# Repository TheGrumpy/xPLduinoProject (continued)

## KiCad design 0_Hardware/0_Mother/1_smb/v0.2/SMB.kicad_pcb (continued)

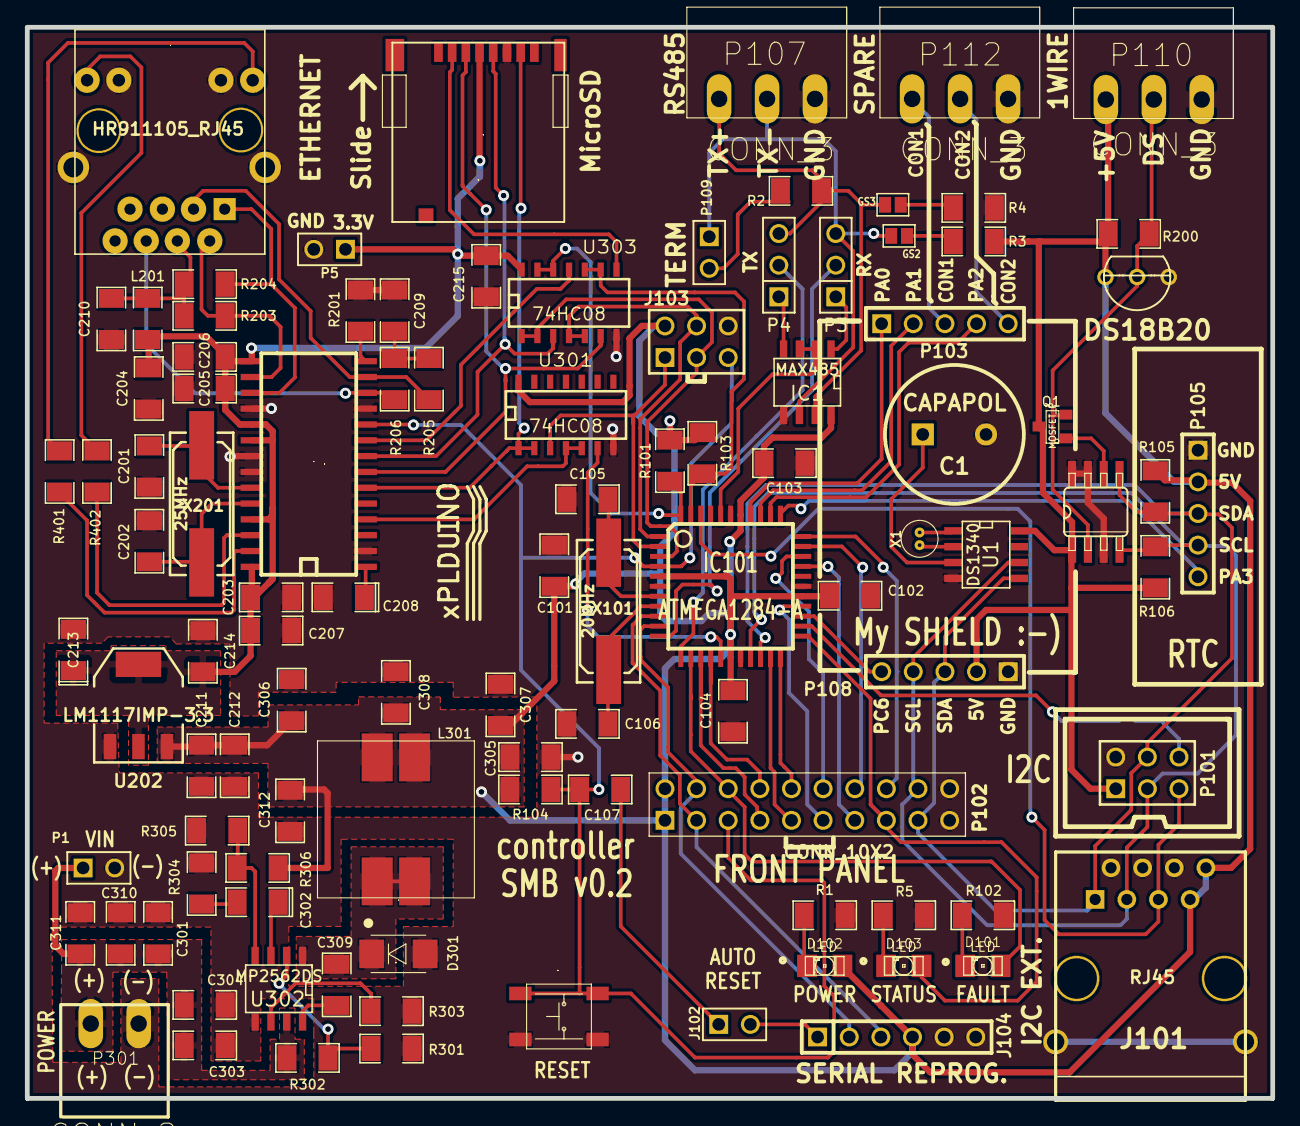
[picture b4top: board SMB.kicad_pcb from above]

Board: 2 copper layers, 100.0 x 86.0 mm, 105 parts (0 on the bottom side), 85 nets.

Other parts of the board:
logo_xplduino: VAL**; logo_xplduino

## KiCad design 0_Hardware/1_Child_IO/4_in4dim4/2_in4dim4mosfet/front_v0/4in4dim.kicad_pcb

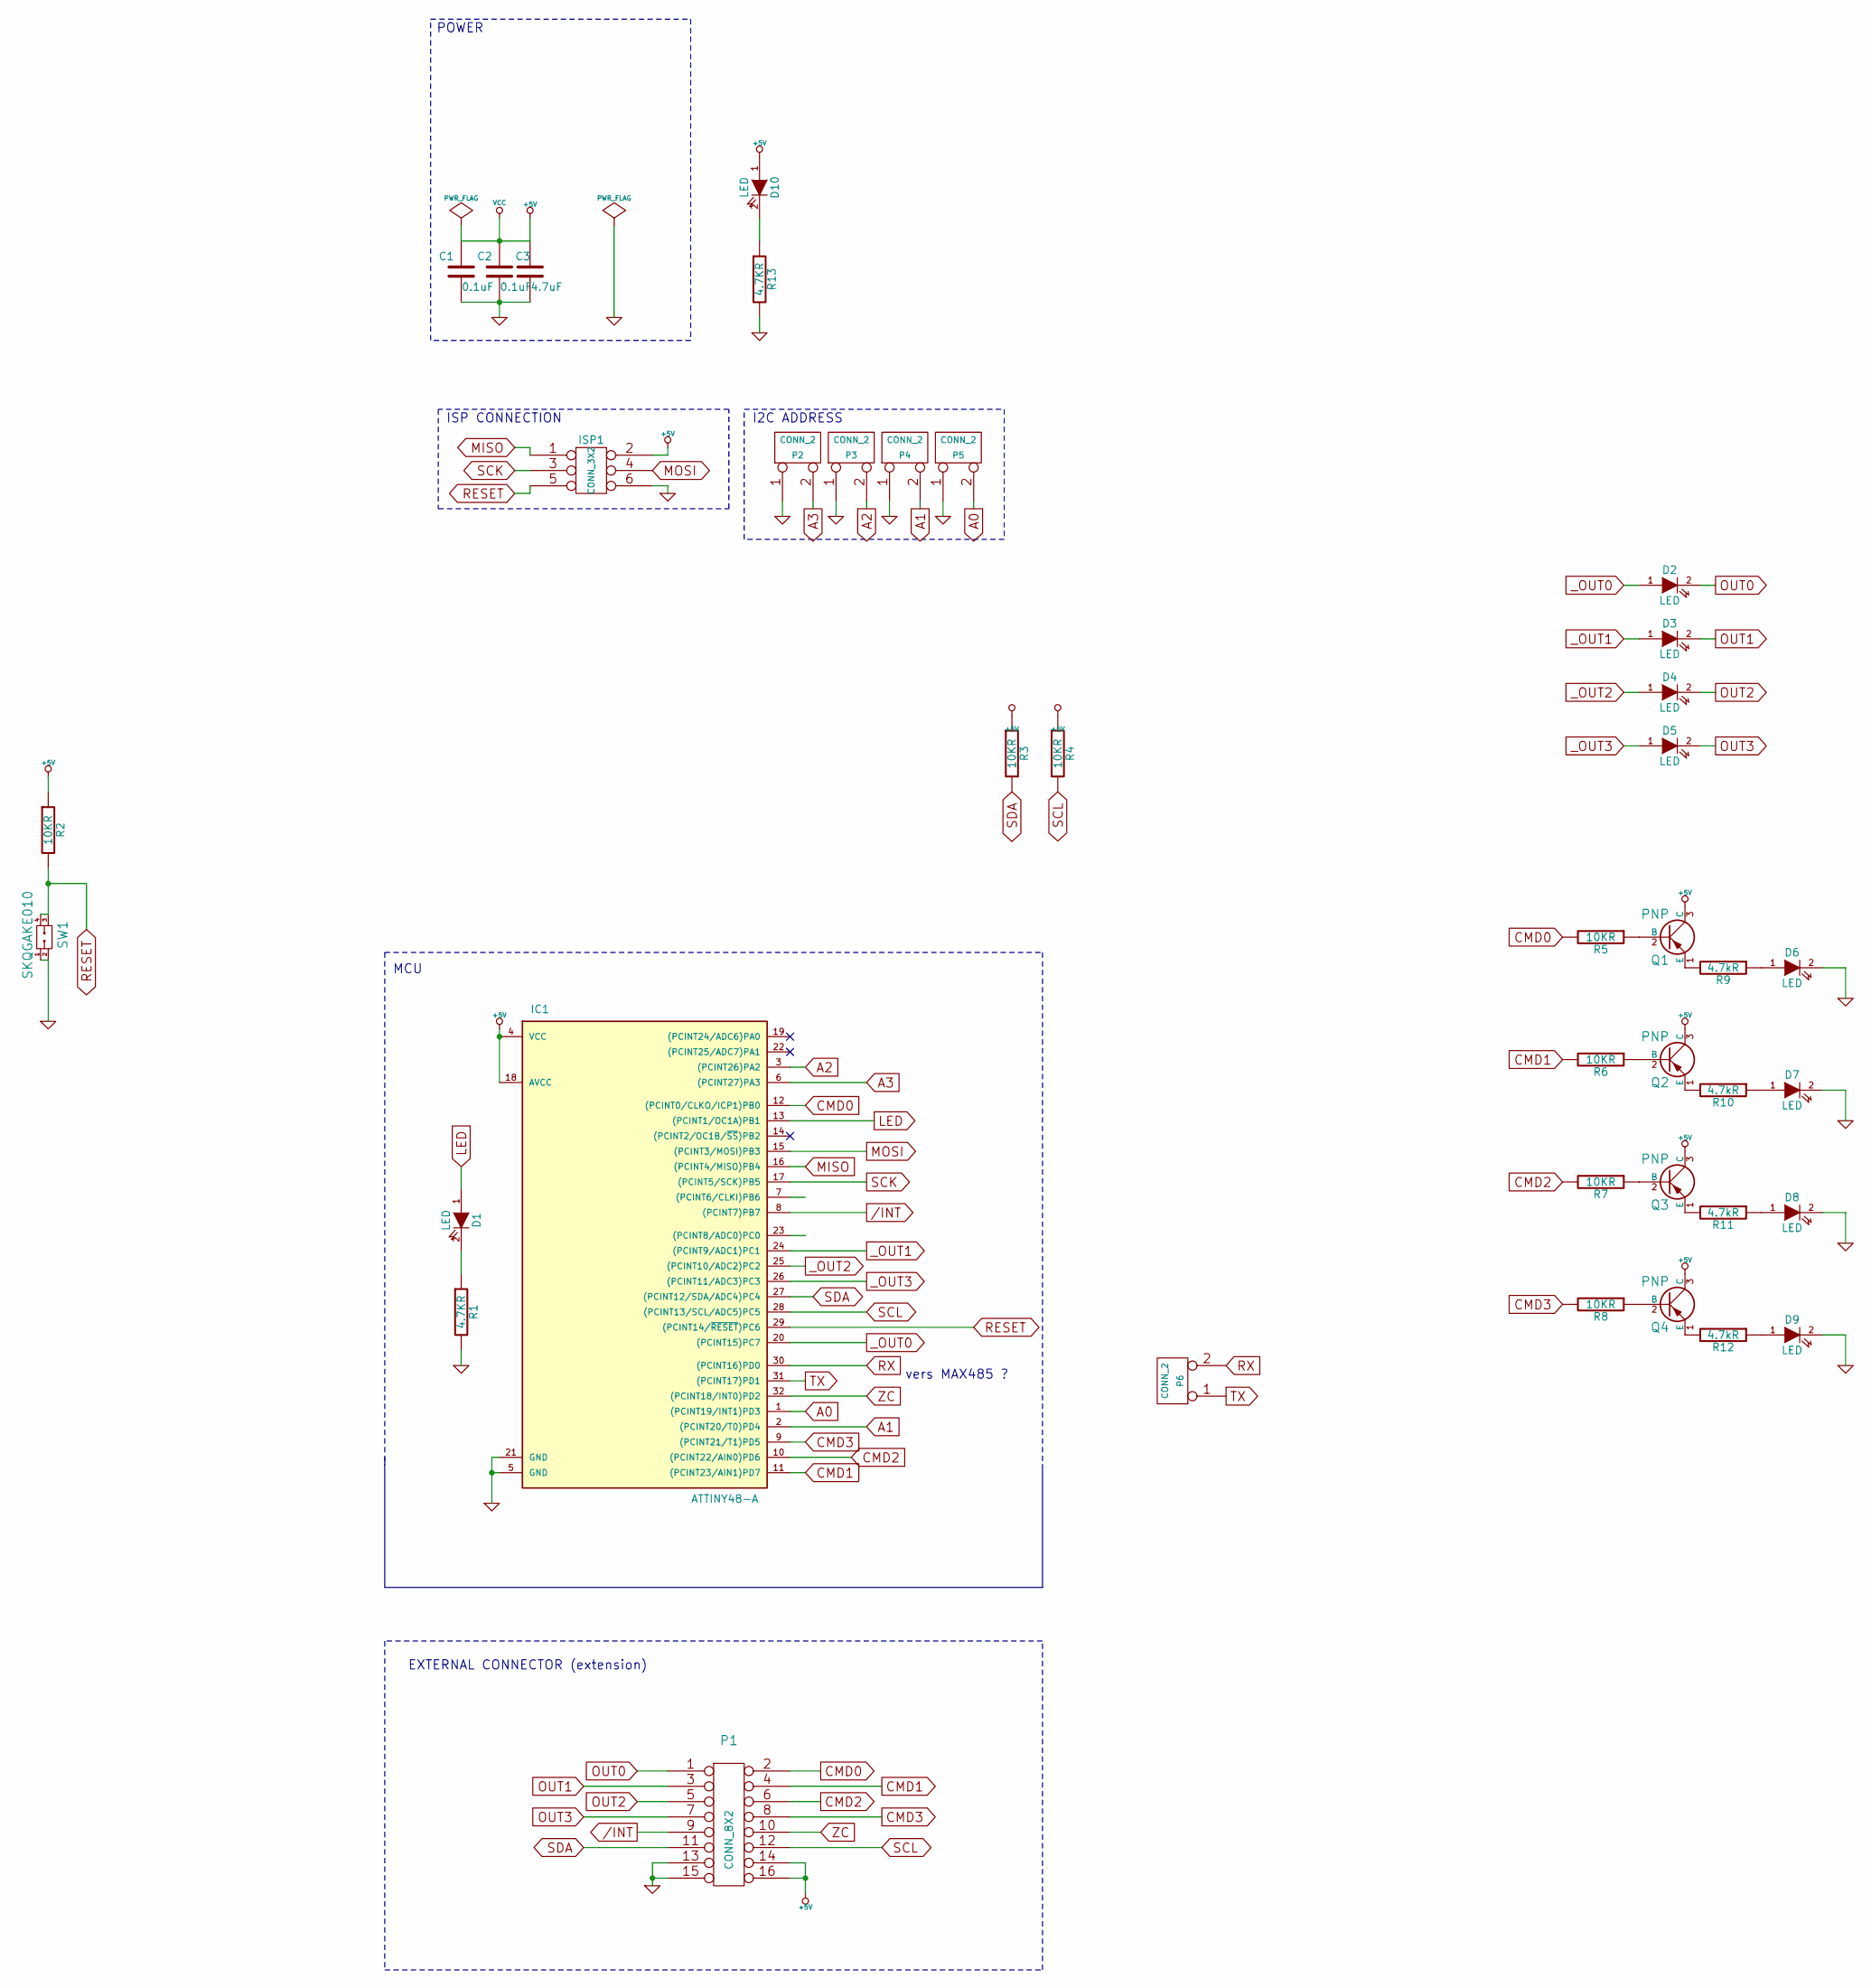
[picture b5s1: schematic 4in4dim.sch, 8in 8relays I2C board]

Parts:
C1, C2: 0.1uF
C3: 4.7uF
D1, D2, D3, D4, D5, D6, D7, D8, D9, D10: LED
IC1: ATTINY48-A; TQFP32
ISP1: CONN_3X2
P1: CONN_8X2
P2, P3, P4, P5, P6: CONN_2
Q1, Q2, Q3, Q4: PNP
R1, R13: 4.7KR
R2, R3, R4, R5, R6, R7, R8: 10KR
R9, R10, R11, R12: 4.7kR
SW1: SKQGAKE010

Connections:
+5V: C1.1, C2.1, C3.1, D10.1 (A), IC1.4 (VCC), IC1.18 (AVCC), ISP1.2, P1.14, P1.16, Q1.3 (C), Q2.3 (C), Q3.3 (C), Q4.3 (C), R2.1, R3.1, R4.1
/INT: IC1.8 ((PCINT7)PB7), P1.9
A0: IC1.1 ((PCINT19/INT1)PD3), P5.2 (PM)
A1: IC1.2 ((PCINT20/T0)PD4), P4.2 (PM)
A2: IC1.3 ((PCINT26)PA2), P3.2 (PM)
A3: IC1.6 ((PCINT27)PA3), P2.2 (PM)
CMD0: IC1.12 ((PCINT0/CLKO/ICP1)PB0), P1.2, R5.2
CMD1: IC1.11 ((PCINT23/AIN1)PD7), P1.4, R6.2
CMD2: IC1.10 ((PCINT22/AIN0)PD6), P1.6, R7.2
CMD3: IC1.9 ((PCINT21/T1)PD5), P1.8, R8.2
GND: C1.2, C2.2, C3.2, D6.2 (K), D7.2 (K), D8.2 (K), D9.2 (K), IC1.5 (GND), IC1.21 (GND), ISP1.6, P1.13, P1.15, P2.1, P3.1, P4.1, P5.1, R1.2, R13.2, SW1.1, SW1.2
LED: D1.1 (A), IC1.13 ((PCINT1/OC1A)PB1)
MISO: IC1.16 ((PCINT4/MISO)PB4), ISP1.1
MOSI: IC1.15 ((PCINT3/MOSI)PB3), ISP1.4
unnamed: D10.2 (K), R13.1
unnamed: D9.1 (A), R12.1
unnamed: D1.2 (K), R1.1
unnamed: D7.1 (A), R10.1
unnamed: Q2.1 (E), R10.2
unnamed: Q2.2 (B), R6.1
unnamed: Q3.1 (E), R11.2
unnamed: D6.1 (A), R9.1
unnamed: Q1.1 (E), R9.2
unnamed: Q4.1 (E), R12.2
unnamed: Q4.2 (B), R8.1
unnamed: D8.1 (A), R11.1
unnamed: Q3.2 (B), R7.1
unnamed: Q1.2 (B), R5.1
OUT0: D2.2 (K), P1.1
OUT1: D3.2 (K), P1.3
OUT2: D4.2 (K), P1.5
OUT3: D5.2 (K), P1.7
RESET: IC1.29 ((PCINT14/~RESET~)PC6), ISP1.5, R2.2, SW1.3, SW1.4
RX: IC1.30 ((PCINT16)PD0), P6.2 (PM)
SCK: IC1.17 ((PCINT5/SCK)PB5), ISP1.3
SCL: IC1.28 ((PCINT13/SCL/ADC5)PC5), P1.12, R4.2
SDA: IC1.27 ((PCINT12/SDA/ADC4)PC4), P1.11, R3.2
TX: IC1.31 ((PCINT17)PD1), P6.1
ZC: IC1.32 ((PCINT18/INT0)PD2), P1.10
_OUT0: D2.1 (A), IC1.20 ((PCINT15)PC7)
_OUT1: D3.1 (A), IC1.24 ((PCINT9/ADC1)PC1)
_OUT2: D4.1 (A), IC1.25 ((PCINT10/ADC2)PC2)
_OUT3: D5.1 (A), IC1.26 ((PCINT11/ADC3)PC3)

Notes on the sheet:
ISP CONNECTION
I2C ADDRESS
POWER
MCU
EXTERNAL CONNECTOR (extension)
vers MAX485 ?

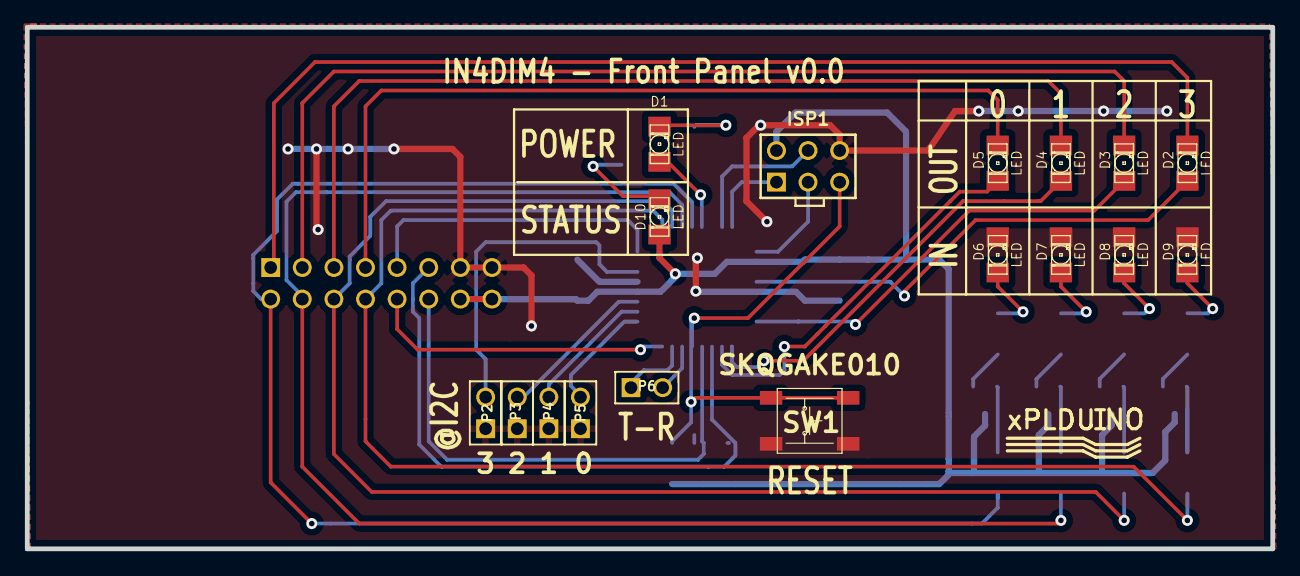
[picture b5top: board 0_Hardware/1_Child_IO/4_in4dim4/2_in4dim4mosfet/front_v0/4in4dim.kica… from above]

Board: 2 copper layers, 100.1 x 41.9 mm, 40 parts (0 on the bottom side), 43 nets.

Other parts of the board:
logo_xplduino: VAL**; logo_xplduino

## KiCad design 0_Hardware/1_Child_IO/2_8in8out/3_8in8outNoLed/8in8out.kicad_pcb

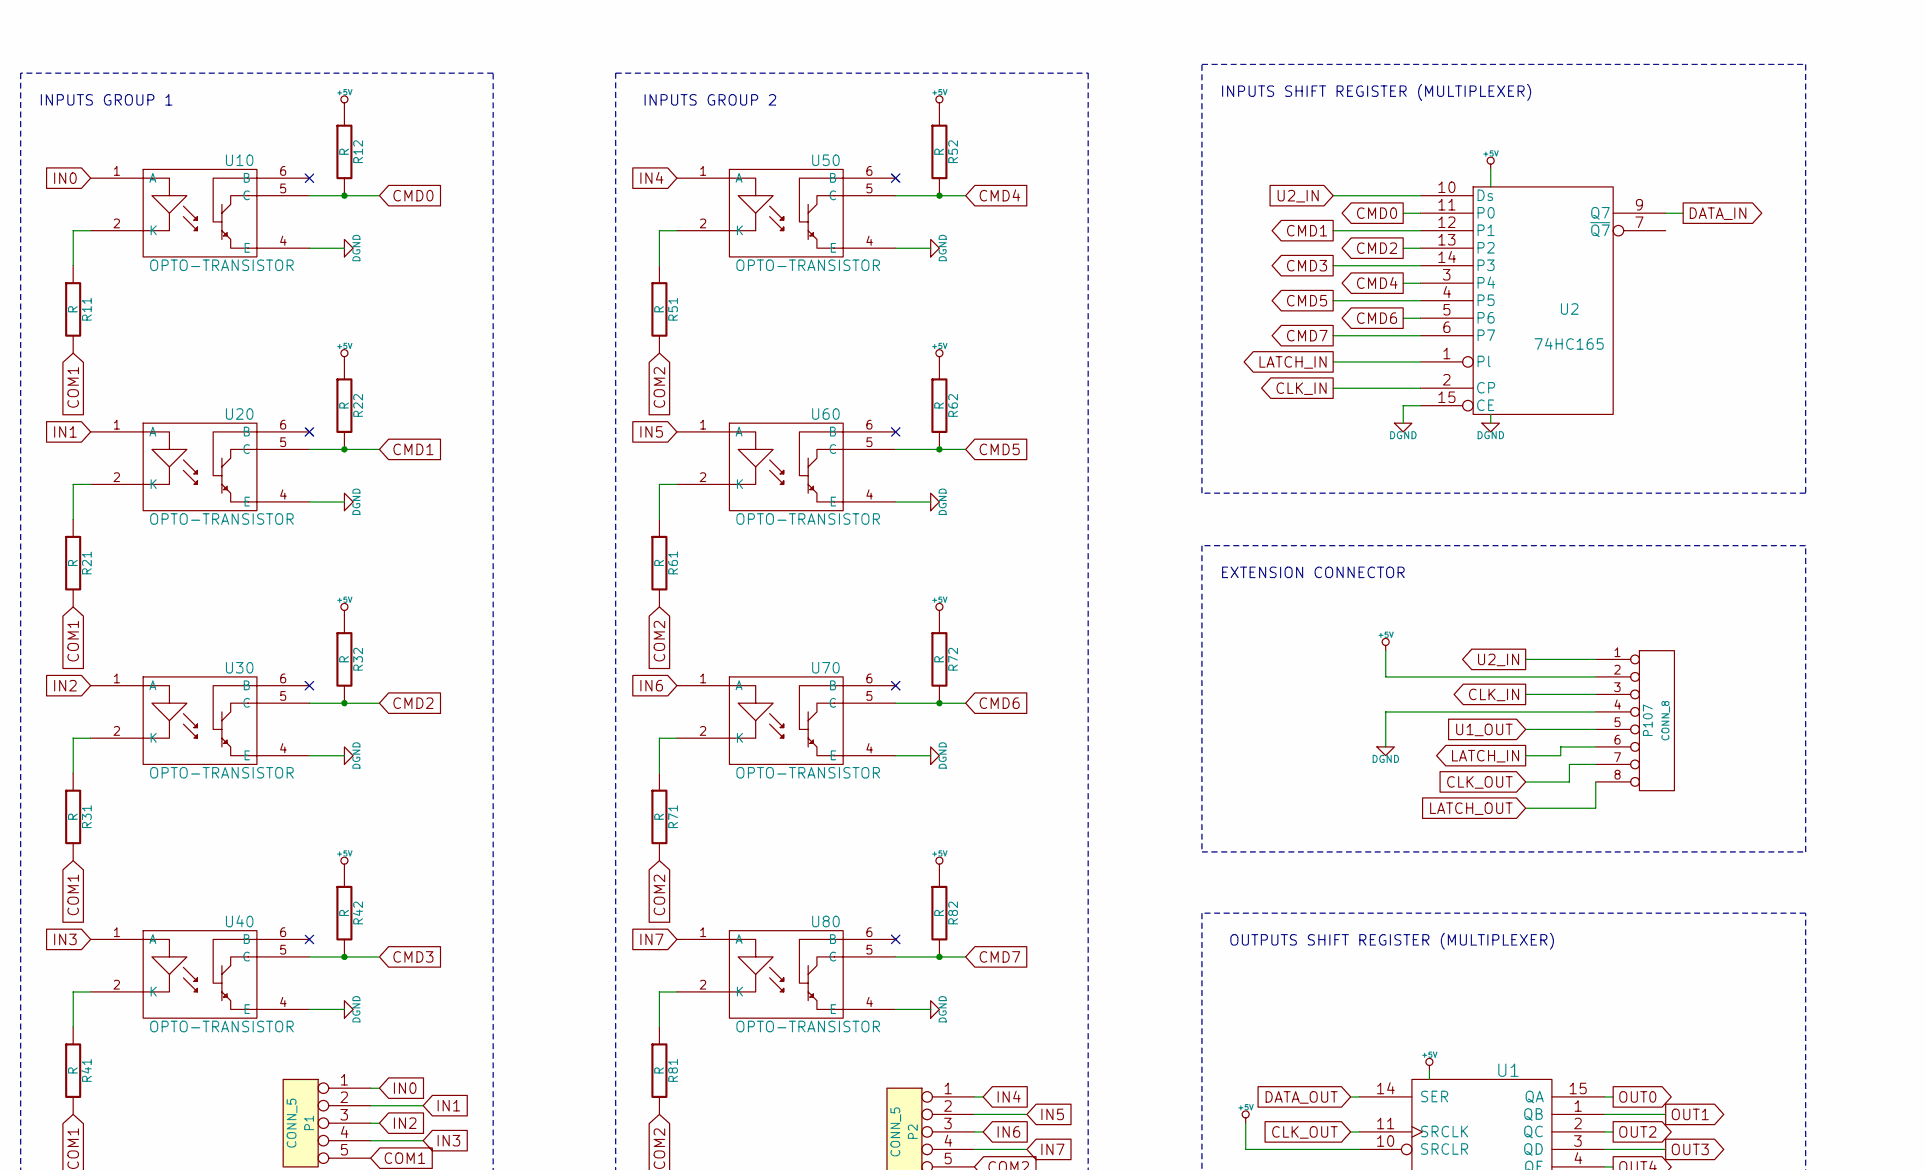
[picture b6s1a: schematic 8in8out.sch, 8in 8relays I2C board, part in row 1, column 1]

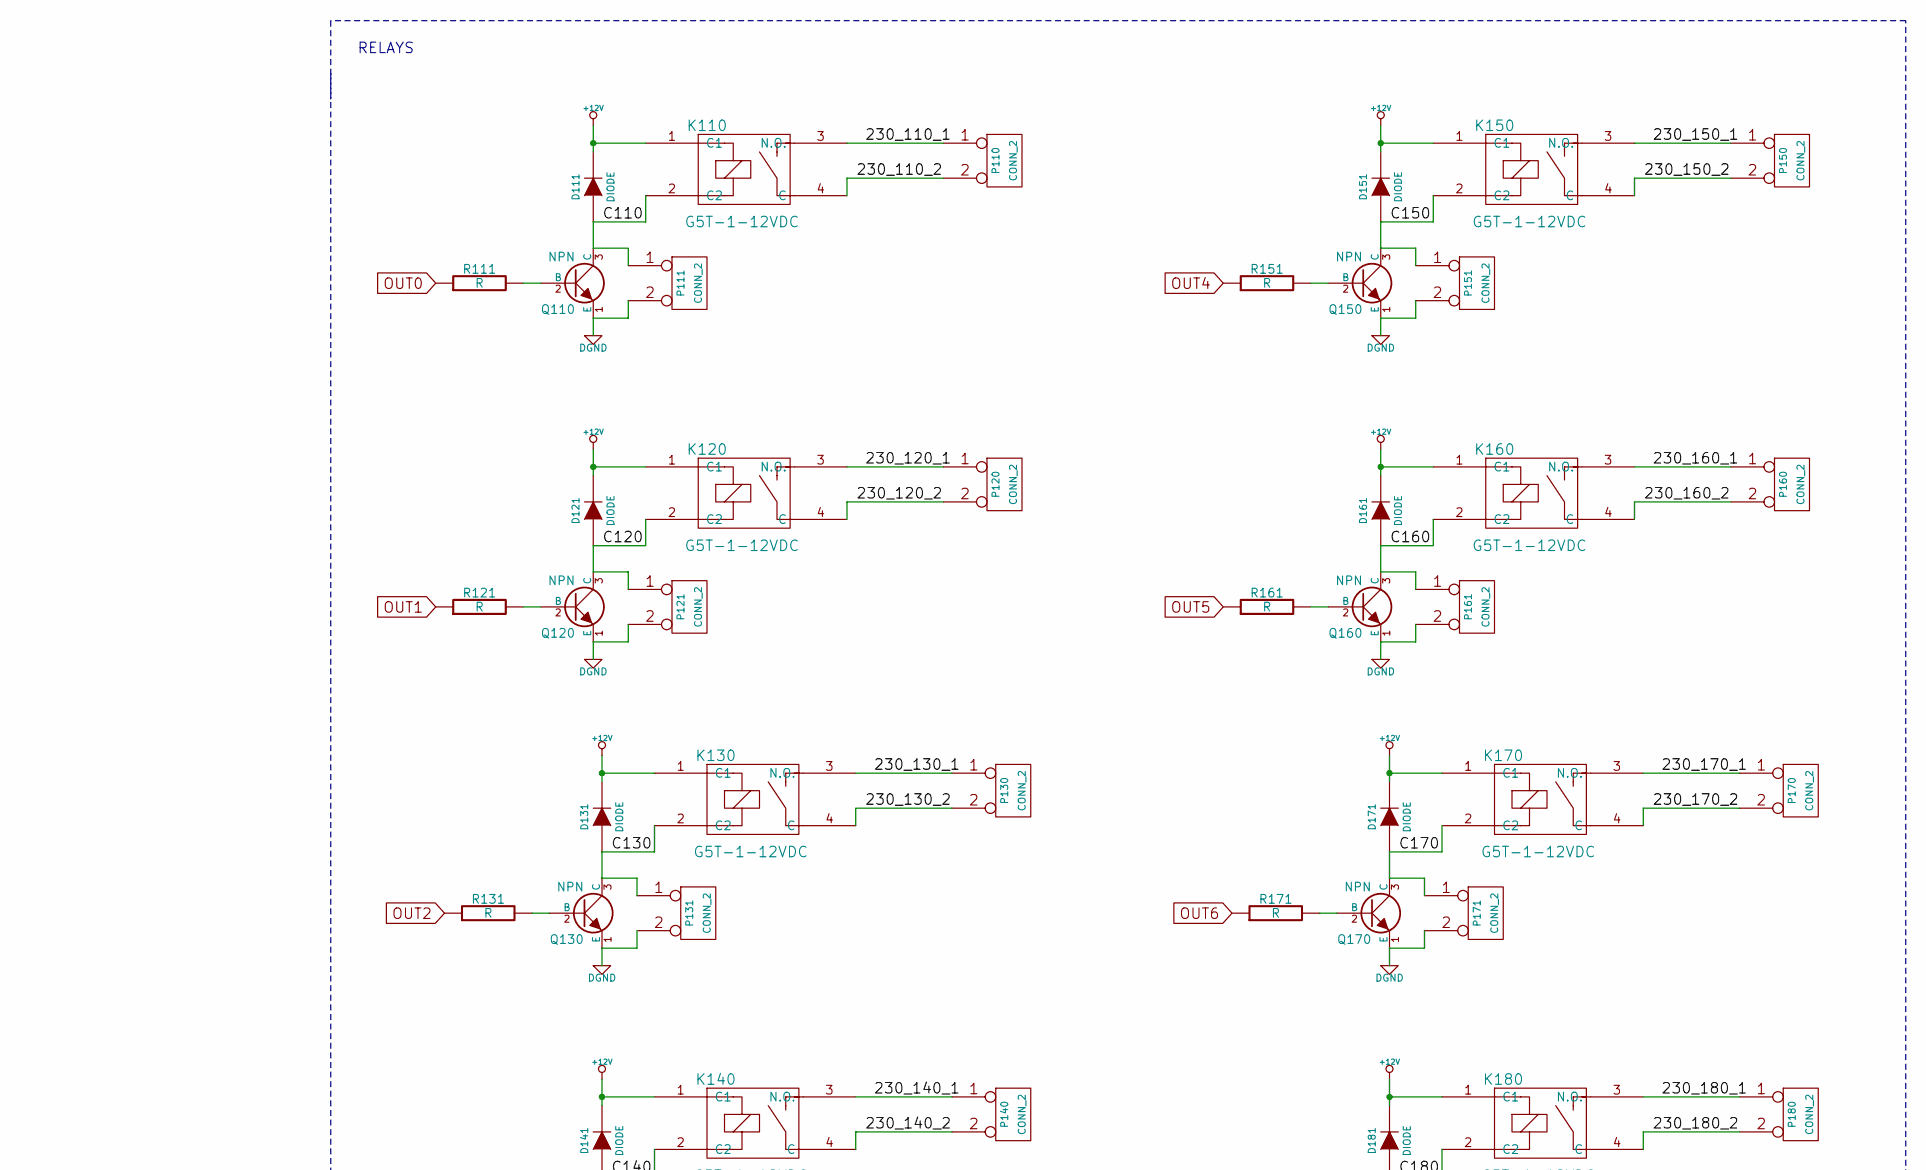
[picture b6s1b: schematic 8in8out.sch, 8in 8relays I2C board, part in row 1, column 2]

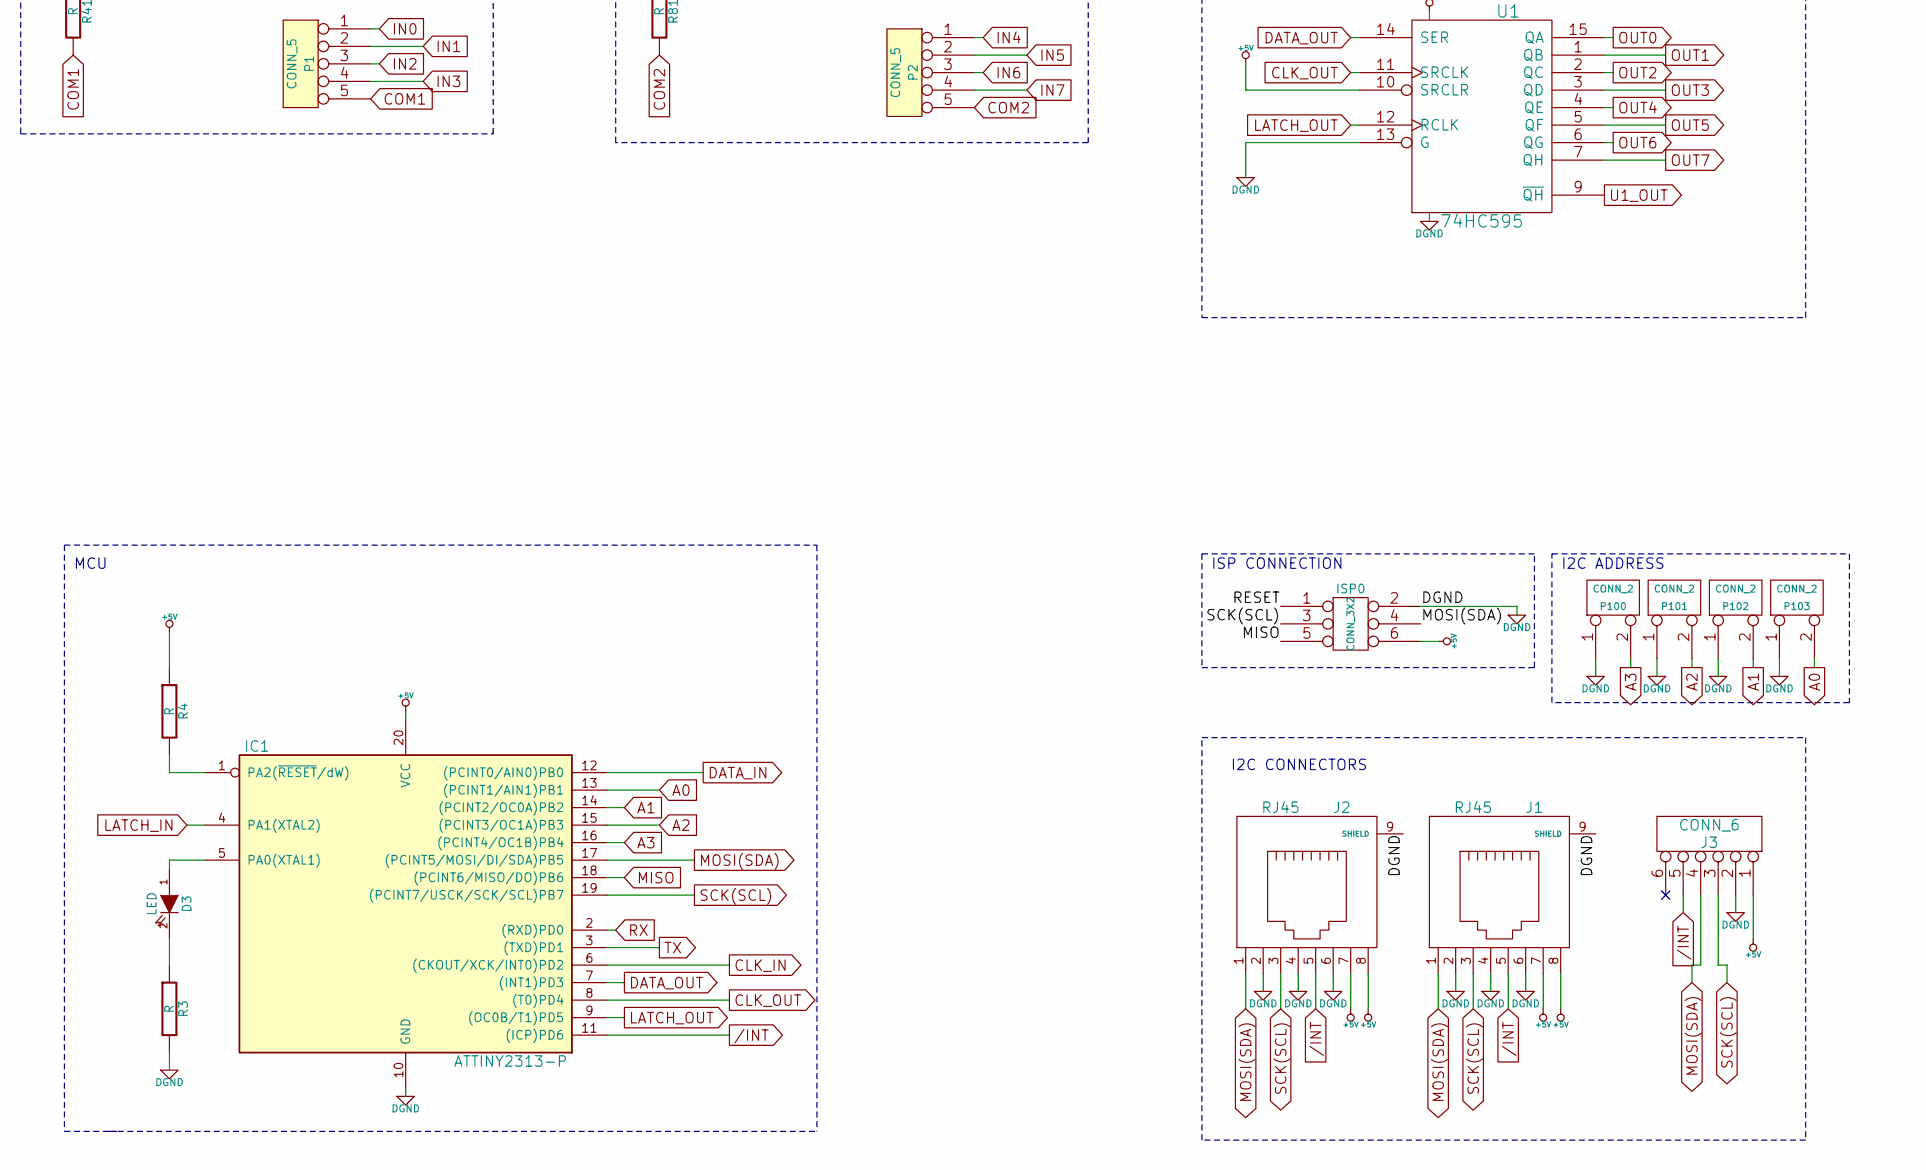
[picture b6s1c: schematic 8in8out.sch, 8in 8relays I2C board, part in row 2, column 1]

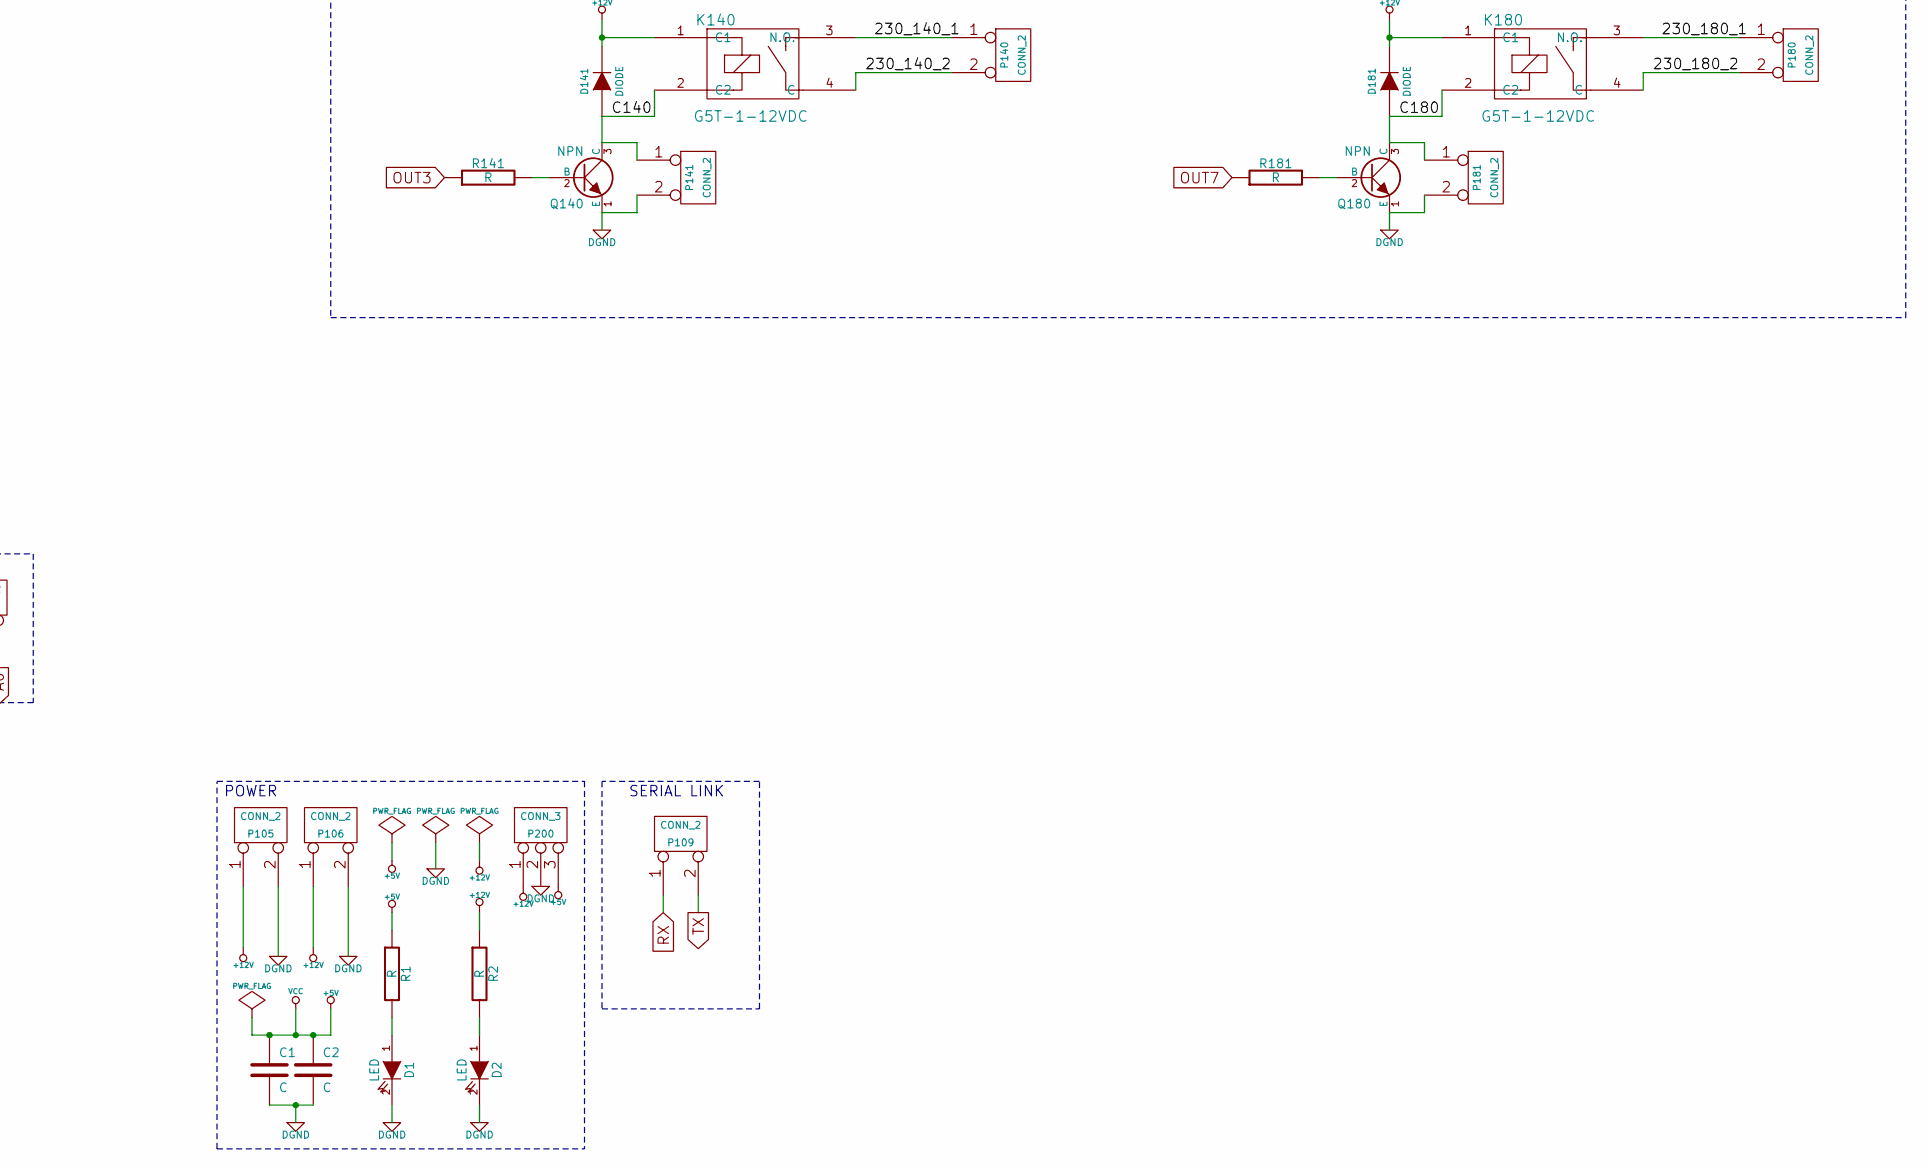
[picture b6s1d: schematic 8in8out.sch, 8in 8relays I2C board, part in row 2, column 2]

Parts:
C1, C2: C
D1, D2, D3: LED
D111, D121, D131, D141, D151, D161, D171, D181: DIODE
IC1: ATTINY2313-P; DIP20
ISP0: CONN_3X2
J1, J2: RJ45
J3: CONN_6
K110, K120, K130, K140, K150, K160, K170, K180: G5T-1-12VDC
P1, P2: CONN_5
P100, P101, P102, P103, P105, P106, P109, P110, P111, P120, P121, P130, P131, P140, P141, P150, P151, P160, P161, P170, P171, P180, P181: CONN_2
P107: CONN_8
P200: CONN_3
Q110, Q120, Q130, Q140, Q150, Q160, Q170, Q180: NPN
R1, R2, R3, R4, R11, R12, R21, R22, R31, R32, R41, R42, R51, R52, R61, R62, R71, R72, R81, R82, R111, R121, R131, R141, R151, R161, R171, R181: R
U1: 74HC595
U2: 74HC165
U10, U20, U30, U40, U50, U60, U70, U80: OPTO-TRANSISTOR

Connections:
+5V: C1.1, C2.1, IC1.20 (VCC), ISP0.6, J1.7, J1.8, J2.7, J2.8, J3.1, P107.2, P200.3, R1.1, R4.1, R12.1, R22.1, R32.1, R42.1, R52.1, R62.1, R72.1, R82.1, U1.10 (SRCLR), U1.16 (VCC), U2.16 (VCC)
+12V: D111.2 (K), D121.2 (K), D131.2 (K), D141.2 (K), D151.2 (K), D161.2 (K), D171.2 (K), D181.2 (K), K110.1 (C1), K120.1 (C1), K130.1 (C1), K140.1 (C1), K150.1 (C1), K160.1 (C1), K170.1 (C1), K180.1 (C1), P105.1, P106.1, P200.1, R2.1
/230_110_1: K110.3 (N.O.), P110.1
/230_110_2: K110.4 (C), P110.2 (PM)
/230_120_1: K120.3 (N.O.), P120.1
/230_120_2: K120.4 (C), P120.2 (PM)
/230_130_1: K130.3 (N.O.), P130.1
/230_130_2: K130.4 (C), P130.2 (PM)
/230_140_1: K140.3 (N.O.), P140.1
/230_140_2: K140.4 (C), P140.2 (PM)
/230_150_1: K150.3 (N.O.), P150.1
/230_150_2: K150.4 (C), P150.2 (PM)
/230_160_1: K160.3 (N.O.), P160.1
/230_160_2: K160.4 (C), P160.2 (PM)
/230_170_1: K170.3 (N.O.), P170.1
/230_170_2: K170.4 (C), P170.2 (PM)
/230_180_1: K180.3 (N.O.), P180.1
/230_180_2: K180.4 (C), P180.2 (PM)
/C110: D111.1 (A), K110.2 (C2), P111.1, Q110.3 (C)
/C120: D121.1 (A), K120.2 (C2), P121.1, Q120.3 (C)
/C130: D131.1 (A), K130.2 (C2), P131.1, Q130.3 (C)
/C140: D141.1 (A), K140.2 (C2), P141.1, Q140.3 (C)
/C150: D151.1 (A), K150.2 (C2), P151.1, Q150.3 (C)
/C160: D161.1 (A), K160.2 (C2), P161.1, Q160.3 (C)
/C170: D171.1 (A), K170.2 (C2), P171.1, Q170.3 (C)
/C180: D181.1 (A), K180.2 (C2), P181.1, Q180.3 (C)
/INT: IC1.11 ((ICP)PD6), J1.5, J2.5, J3.5
A0: IC1.13 ((PCINT1/AIN1)PB1), P103.2 (PM)
A1: IC1.14 ((PCINT2/OC0A)PB2), P102.2 (PM)
A2: IC1.15 ((PCINT3/OC1A)PB3), P101.2 (PM)
A3: IC1.16 ((PCINT4/OC1B)PB4), P100.2 (PM)
CLK_IN: IC1.6 ((CKOUT/XCK/INT0)PD2), P107.3, U2.2 (CP)
CLK_OUT: IC1.8 ((T0)PD4), P107.7, U1.11 (SRCLK)
CMD0: R12.2, U2.11 (P0), U10.5 (C)
CMD1: R22.2, U2.12 (P1), U20.5 (C)
CMD2: R32.2, U2.13 (P2), U30.5 (C)
CMD3: R42.2, U2.14 (P3), U40.5 (C)
CMD4: R52.2, U2.3 (P4), U50.5 (C)
CMD5: R62.2, U2.4 (P5), U60.5 (C)
CMD6: R72.2, U2.5 (P6), U70.5 (C)
CMD7: R82.2, U2.6 (P7), U80.5 (C)
COM1: P1.5, R11.2, R21.2, R31.2, R41.2
COM2: P2.5, R51.2, R61.2, R71.2, R81.2
DATA_IN: IC1.12 ((PCINT0/AIN0)PB0), U2.9 (Q7)
DATA_OUT: IC1.7 ((INT1)PD3), U1.14 (SER)
DGND: C1.2, C2.2, D1.2 (K), D2.2 (K), IC1.10 (GND), ISP0.2, J1.2, J1.4, J1.6, J1.9 (SHIELD), J2.2, J2.4, J2.6, J2.9 (SHIELD), J3.2, P100.1, P101.1, P102.1, P103.1, P105.2 (PM), P106.2 (PM), P107.4, P111.2 (PM), P121.2 (PM), P131.2 (PM), P141.2 (PM), P151.2 (PM), P161.2 (PM), P171.2 (PM), P181.2 (PM), P200.2 (PM), Q110.1 (E), Q120.1 (E), Q130.1 (E), Q140.1 (E), Q150.1 (E), Q160.1 (E), Q170.1 (E), Q180.1 (E), R3.2, U1.8 (GND), U1.13 (G), U2.8 (GND), U2.15 (CE), U10.4 (E), U20.4 (E), U30.4 (E), U40.4 (E), U50.4 (E), U60.4 (E), U70.4 (E), U80.4 (E)
IN0: P1.1, U10.1 (A)
IN1: P1.2, U20.1 (A)
IN2: P1.3, U30.1 (A)
IN3: P1.4, U40.1 (A)
IN4: P2.1, U50.1 (A)
IN5: P2.2, U60.1 (A)
IN6: P2.3, U70.1 (A)
IN7: P2.4, U80.1 (A)
LATCH_IN: IC1.4 (PA1(XTAL2)), P107.6, U2.1 (Pl)
LATCH_OUT: IC1.9 ((OC0B/T1)PD5), P107.8, U1.12 (RCLK)
MISO: IC1.18 ((PCINT6/MISO/DO)PB6), ISP0.5
MOSI(SDA): IC1.17 ((PCINT5/MOSI/DI/SDA)PB5), ISP0.4, J1.1, J2.1, J3.4
unnamed: R61.1, U60.2 (K)
unnamed: R21.1, U20.2 (K)
unnamed: R31.1, U30.2 (K)
unnamed: R41.1, U40.2 (K)
unnamed: R51.1, U50.2 (K)
unnamed: R71.1, U70.2 (K)
unnamed: R81.1, U80.2 (K)
unnamed: Q180.2 (B), R181.2
unnamed: Q150.2 (B), R151.2
unnamed: Q160.2 (B), R161.2
unnamed: Q170.2 (B), R171.2
unnamed: Q130.2 (B), R131.2
unnamed: Q110.2 (B), R111.2
unnamed: Q120.2 (B), R121.2
unnamed: Q140.2 (B), R141.2
unnamed: IC1.1 (PA2(~RESET~/dW)), R4.2
unnamed: D3.1 (A), IC1.5 (PA0(XTAL1))
unnamed: D3.2 (K), R3.1
unnamed: R11.1, U10.2 (K)
unnamed: D2.1 (A), R2.2
unnamed: D1.1 (A), R1.2
OUT0: R111.1, U1.15 (QA)
OUT1: R121.1, U1.1 (QB)
OUT2: R131.1, U1.2 (QC)
OUT3: R141.1, U1.3 (QD)
OUT4: R151.1, U1.4 (QE)
OUT5: R161.1, U1.5 (QF)
OUT6: R171.1, U1.6 (QG)
OUT7: R181.1, U1.7 (QH)
RX: IC1.2 ((RXD)PD0), P109.1
SCK(SCL): IC1.19 ((PCINT7/USCK/SCK/SCL)PB7), ISP0.3, J1.3, J2.3, J3.3
TX: IC1.3 ((TXD)PD1), P109.2 (PM)
U1_OUT: P107.5, U1.9 (~QH)
U2_IN: P107.1, U2.10 (Ds)

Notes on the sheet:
ISP CONNECTION
I2C ADDRESS
POWER
I2C CONNECTORS
MCU
INPUTS GROUP 1
INPUTS GROUP 2
INPUTS SHIFT REGISTER (MULTIPLEXER)
RELAYS
OUTPUTS SHIFT REGISTER (MULTIPLEXER)
EXTENSION CONNECTOR
SERIAL LINK

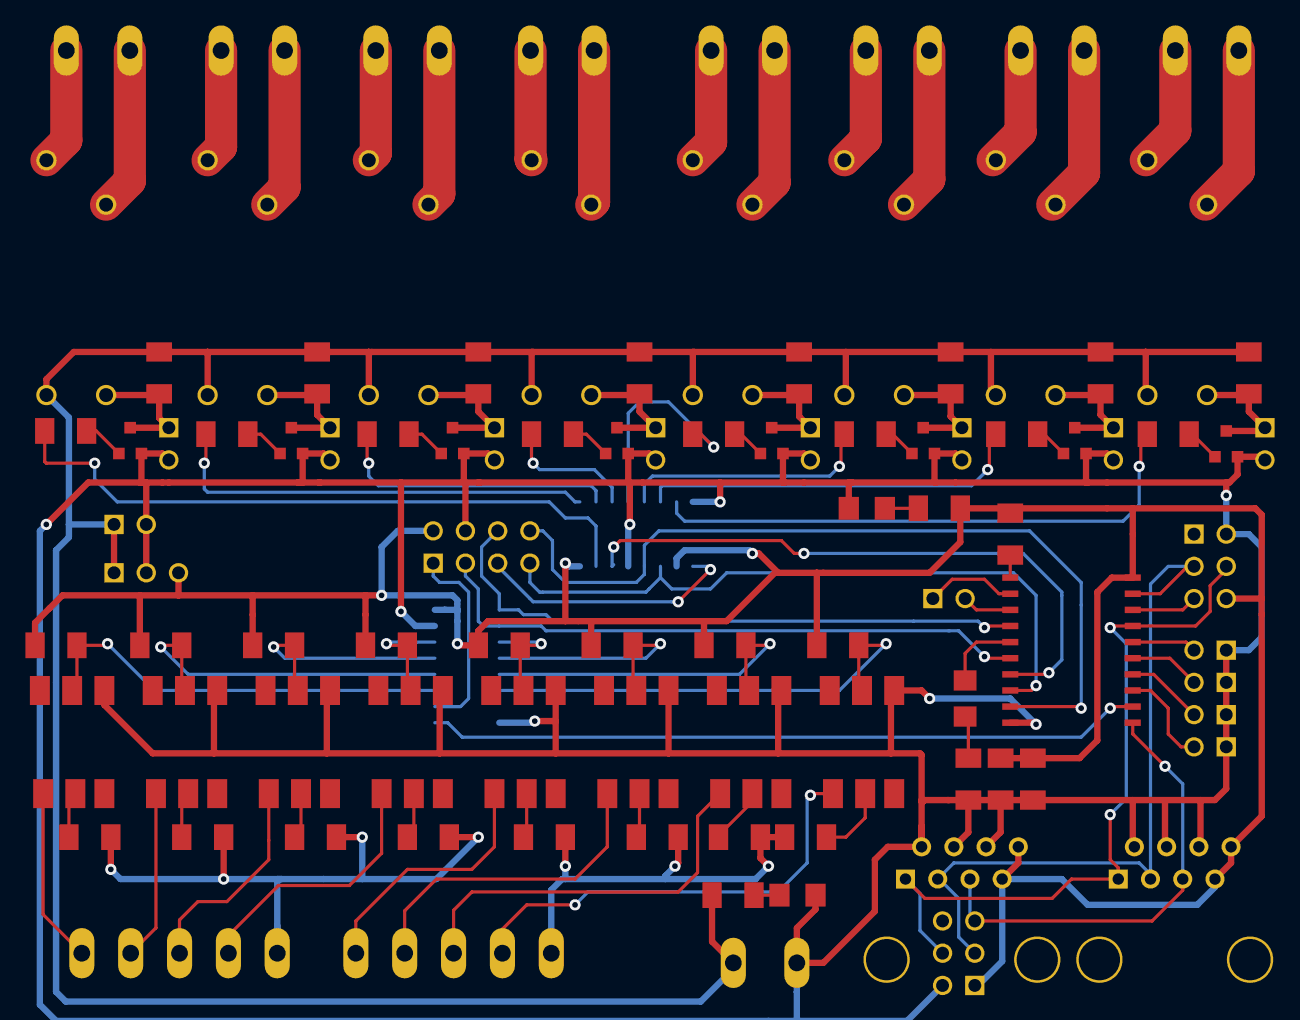
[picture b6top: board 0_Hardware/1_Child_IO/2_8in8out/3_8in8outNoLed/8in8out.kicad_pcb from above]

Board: 2 copper layers, 99 parts (0 on the bottom side), 92 nets.

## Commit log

2014-10-03 Ajout projet xPLduino
2014-10-05 Mise à jour du PCB Front Panel in4dim4mosfet -> Inversion des broches dans le schéma pour faciliter le routage * CMD0 Broche7 => Broche 10 de l'attiny * CMD1 Broche8 => Broche 9 de l'attiny * CMD2 Br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
    Mise à jour nom dans les gerber SMB V0.0 pour éviter les pb Smartgit
2014-10-08 Mise à jour du pcb in4dim4mosfet front : - Retournerment à 180° du connecteur Back Panel / Front Panel et alignement sur l'axe x avec le connecteur back panel - Re-routage
2014-10-09 Mise à jour du Front Panel in4dim4 mosfet
    - Ecartement des composants
    - Inversion des broches de sorties de l'attinye OUT0 à 4 pour faciliter le routage
    - Ajout de la sérigraphie
2014-10-11 MàJ du pcb front panel in4dim4 mosfet
    Décalage vers la gauche des leds pawer status
    Décalage vers le haut des cavaliers @I2C
2014-10-25 Mise à jour du manager : - Suppression des fenêtre pop-up - Optimisation de montage de projet - Modification du mode de compilation - Visualisation des noeuds compilé - Enregistrement des .hez dans l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
2014-10-27 Mise à jour du manager : - Log de génération et de chargement dans un nouvel onglet - Mode de génération et de chargment depuis l'onglet projet - Création de backup d'enregistrement des versions
2014-11-02 Résolution bugs mineurs manager + Essais RF
2014-11-10 Correction bugs mineur
2014-11-11 Mise à jour du manager : - Ouverture de tous les fichiers .dom - Suppression des instances via touche suppr - Résolution des bugs à l'enregistrement
2014-11-15 Correction bug enregistrement Correction bug compilation
2014-11-16 mis à jour de la carte de puissance et de la front panel
2014-11-17 Ajout doublage piste 140M (oubli)
2014-11-19 Carte de puissance dimmer - modification du connecteur 20 broches: doublement de 5V et GND et optimisation pinout - modification empreinte des optos 4 canaux et single (création boitier DDIP16 et DDI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
2014-11-19 Front panel dimmer: - passé tous les composants sauf leds et bouton reset face dessous pour libérer la place pour la sérigraphie - suite modif pinout connecteur 20 pins côté puissance - reroutage (TO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
2014-11-23 finalisation dimmer (front et back panel)
2014-11-23 mise à jour smb v0.2 (schéma, package, routage). Todo: vérifier les packages des nouveaux composants
2014-11-24 mise à jour de la carte 8in8r: - passage en face inférieur de l'ULN2803 afin de dégager de la place pour le connecteur front panel - remplacement des 8 opto CNY17 par 2 équivalents 4 channel - rerout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
2014-11-24 déplacement fichiers front carte 8in8r dans sous dossier v0.1
2014-11-24 evolution de v0.1: - passage LED en CMS - bp reset en CMS
2014-11-25 IN4DIM4: remplacement empreinte PNP par SOT-23 standard
2014-11-25 IN8R8: remplacement empreinte PNP et NPN par SOT-23 standard, agencement des leds comme carte IN4DIM4
2014-11-25 SMB v0.2: remplacement composant mosfet par type P
2014-11-28 SMB v0.2: descendu de 1mm supercapa car diam 13.5 + U201 nouvel empreinte SOIC-8 (pads allongés pour faciliter soudure)
2014-11-28 skilkscreen
2014-11-28 echange format resistance nulle (RPx) pour plus grand longueur
2014-11-28 skilkscreen + gerber
2014-11-28 gerber
2015-04-06 Change Project list to Dictionary.
2015-04-06 Revert "Change Project list to Dictionary."
    This reverts commit 350ae78a5a401ce2fe8e5373f65fe2f44b8afedf.
2015-04-06 Change ListProject from list to dictionary.
2015-06-30 Revert "skilkscreen + gerber"
    This reverts commit f66d5581d9f6963949e67885314110cfecfc1ca6.
2015-06-30 Revert "gerber"
    This reverts commit b313a58f77274340a4ddfbe6eabdaad50f0b77f6.
